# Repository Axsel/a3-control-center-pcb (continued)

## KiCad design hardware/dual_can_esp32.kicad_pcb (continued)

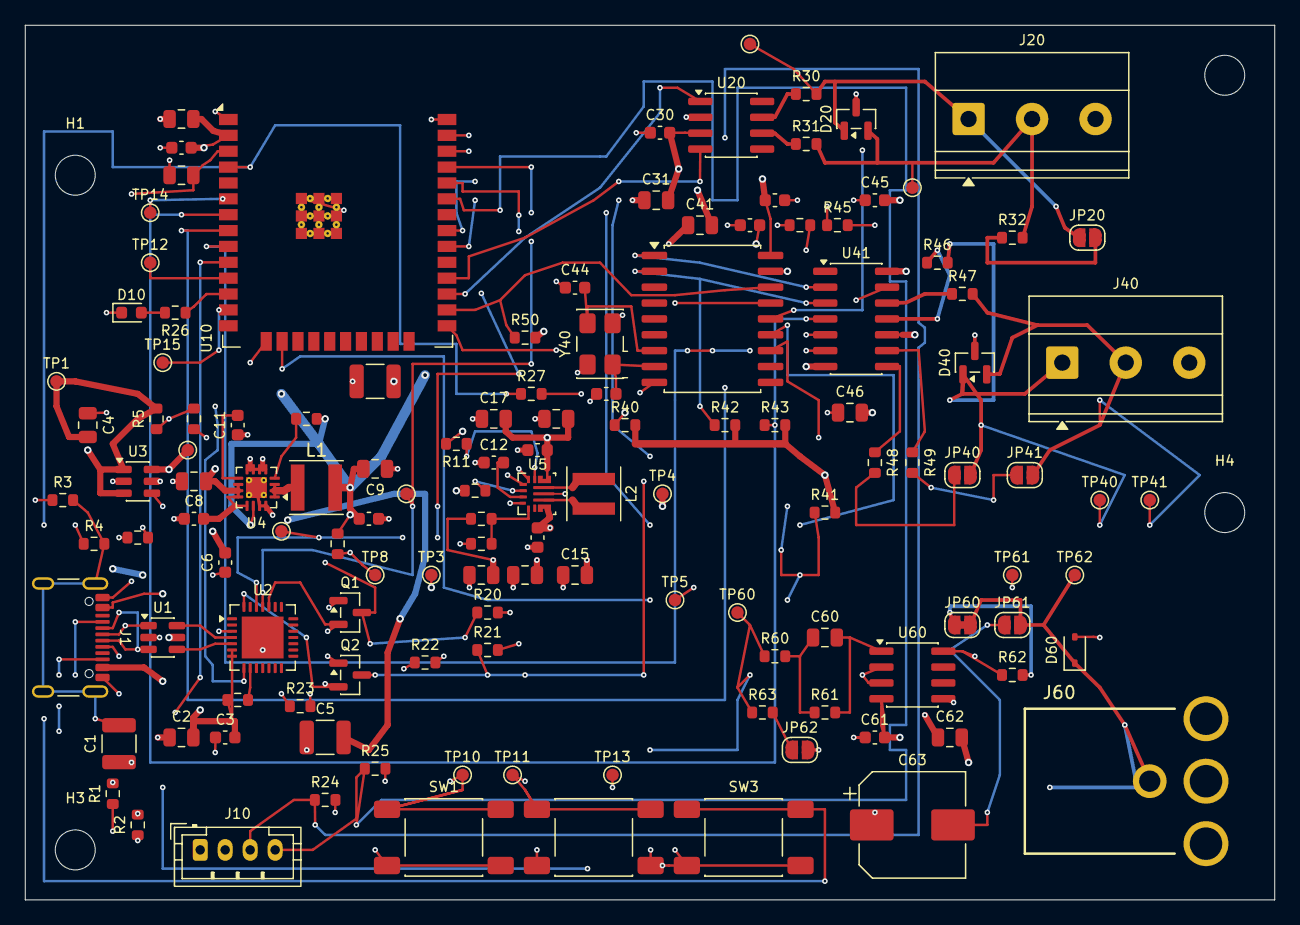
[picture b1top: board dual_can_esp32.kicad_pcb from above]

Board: 4 copper layers, 100.0 x 70.0 mm, 134 parts (0 on the bottom side), 77 nets.

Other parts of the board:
H1, H2, H3, H4: MountingHole_3.2mm_M3

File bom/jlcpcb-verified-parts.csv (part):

Reference,Manufacturer,Manufacturer Part,LCSC Part,Verification date,Catalog state at check,Source,Notes
R1 R2,UNI-ROYAL,0603WAF5101T5E,C23186,2026-10-04,In stock,https://www.lcsc.com/product-detail/C23186.html,"5.1 kohm 1% 100 mW 75 V 0603"
R3,UNI-ROYAL,0603WAF1004T5E,C22935,2026-10-04,In stock,https://www.lcsc.com/product-detail/C22935.html,"1 Mohm 1% 100 mW 75 V 0603"
R5,UNI-ROYAL,0603WAF2212T5E,C25961,2026-10-04,In stock,https://www.lcsc.com/product-detail/C25961.html,"22.1 kohm 1% 100 mW 75 V 0603"
R6,UNI-ROYAL,0603WAF4752T5E,C23061,2026-10-04,In stock,https://www.lcsc.com/product-detail/C23061.html,"47.5 kohm 1% 100 mW 75 V 0603"
R7 R26,UNI-ROYAL,0603WAF1001T5E,C21190,2026-10-04,In stock,https://www.lcsc.com/product-detail/C21190.html,"1 kohm 1% 100 mW 75 V 0603"
R8,UNI-ROYAL,0603WAF2872T5E,C22928,2026-10-04,Low stock (300 shown),https://www.lcsc.com/product-detail/C22928.html,"28.7 kohm 1% 100 mW 75 V 0603; TPS2553 current-limit setpoint"
R9 R11 R20 R21 R22 R23 R27 R40 R41 R42 R43 R44 R45 R50,UNI-ROYAL,0603WAF1002T5E,C25804,2026-10-04,In stock,https://www.lcsc.com/product-detail/C25804.html,"10 kohm 1% 100 mW 75 V 0603"
R10 R14,UNI-ROYAL,0603WAF1003T5E,C25803,2026-10-04,In stock,https://www.lcsc.com/product-detail/C25803.html,"100 kohm 1% 100 mW 75 V 0603"
R12,UNI-ROYAL,0603WAF6803T5E,C25822,2026-10-04,In stock,https://www.lcsc.com/product-detail/C25822.html,"680 kohm 1% 100 mW 75 V 0603; 5V_FT feedback"
R13,UNI-ROYAL,0603WAF1303T5E,C22795,2026-10-04,In stock,https://www.lcsc.com/product-detail/C22795.html,"130 kohm 1% 100 mW 75 V 0603; 5V_FT feedback"
R30 R31 R46 R47,UNI-ROYAL,0603WAF0000T5E,C21189,2026-10-04,In stock,https://www.lcsc.com/product-detail/C21189.html,"0 ohm 100 mW 0603 fitted common-mode-choke bypasses"
R32,UNI-ROYAL,0603WAF1200T5E,C22787,2026-10-04,In stock,https://www.lcsc.com/product-detail/C22787.html,"120 ohm 1% 100 mW 0603 selectable CAN_HS termination"
R48 R49,UNI-ROYAL,0603WAF1201T5E,C22765,2026-10-04,In stock,https://www.lcsc.com/product-detail/C22765.html,"1.2 kohm 1% 100 mW 0603 configurable FT-CAN line terminations"
R60,UNI-ROYAL,0603WAF330JT5E,C23140,2026-10-04,In stock,https://www.lcsc.com/product-detail/C23140.html,"33 ohm 1% 100 mW 0603 DAC isolation"
R62,UNI-ROYAL,0603WAF750JT5E,C4275,2026-10-04,In stock,https://www.lcsc.com/product-detail/C4275.html,"75 ohm 1% 100 mW 0603 video source termination"
D20 D40,Nexperia,PESD2CAN24T-QR,C28933048,2026-10-04,In stock,https://www.lcsc.com/product-detail/C28933048.html,"Reel suffix R; exact PESD2CAN24T-Q device and SOT-23 package"
D60,HXY MOSFET,HPESD5V0U1BA-Q,C25503782,2026-10-05,In stock (900 shown in LCSC catalog; owner reports JLC inventory available),https://www.lcsc.com/product-detail/C25503782.html,"Revision A prototype alternative to Nexperia PESD5V0U1BA-QX/C7508796: same bidirectional 5 V SOD-323 topology; 2.5 pF max; not AEC-Q101; narrower -40 to +125 C operating range and higher 1 uA leakage"
J1,Global Connector Technology,USB4105-GF-A,C3020560,2026-10-04,Out of stock,https://www.lcsc.com/product-detail/USB-Connectors_Global-Co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,"Exact approved connector; mixed SMT contacts/PTH stakes still require assembly-process confirmation"
J10,JST,B4B-PH-K-S(LF)(SN),C131334,2026-10-04,In stock,https://www.lcsc.com/product-detail/C131334.html,"Exact keyed vertical PH-series 4-pin 2.00 mm connector; required JLC manual/wave assembly"
J20 J40,Phoenix Contact,1715734,C480520,2026-10-04,In stock,https://www.lcsc.com/product-detail/C480520.html,"Exact three-independent-position 5.08 mm terminal block; required JLC manual/wave assembly; never substitute internally commoned -B- variant"
J60,Same Sky,RCJ-014,C4991844,2026-10-05,In stock (64 snapshot),https://jlcpcb.com/partdetail/CUI-RCJ014/C4991844,"Yellow right-angle THT RCA; official RCJ-01 footprint; manufacturer pin 1 shell and pin 2 center; JLC manual/wave assembly required"
U1,STMicroelectronics,USBLC6-2SC6,C7519,2026-10-04,Exact product page found,https://www.lcsc.com/product-detail/Diodes-ESD_STMicroelectr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,"Recheck JLC assembly inventory, not only LCSC distributor stock"
U2,Silicon Labs,CP2102N-A02-GQFN28R,C964632,2026-10-04,In stock (40263 shown),https://www.lcsc.com/product-detail/C964632.html,"R is Silicon Labs' optional tape-and-reel suffix; same A02 firmware/hardware revision, temperature grade, QFN28 package, pinout, and land pattern as the former tray-order code"
U3,Texas Instruments,TPS2553DBVR,C55266,2026-10-04,In stock,https://www.lcsc.com/product-detail/C55266.html,"Exact constant-current (non -1 latch-off) variant"
U4,Texas Instruments,TPS62132RGTR,C81563,2026-10-04,Exact product page found,https://www.lcsc.com/product-detail/C81563.html,"Recheck stock and JLC assembly classification at order time"
U5,Texas Instruments,TPS63070RNMR,C109322,2026-10-04,In stock,https://www.lcsc.com/product-detail/C109322.html,"Project-local RNM0015A footprint passed independent dimensional audit; JLC DFM review of the documented pads 4/5 heel relief remains required"
U10,Espressif,ESP32-WROOM-32E-N4,C701341,2026-10-04,In stock,https://www.lcsc.com/product-detail/WIFI-Modules_Espressif-S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,"Exact approved 4 MB PCB-antenna module"
U20,Texas Instruments,TCAN332DR,C73651,2026-10-04,In stock,https://www.lcsc.com/product-detail/C73651.html,"Exact SOIC-8 reel variant"
U40,Microchip,MCP2515T-I/SO,C153782,2026-10-05,In stock (8022 shown; selected in JLC workbook),https://www.lcsc.com/product-detail/C153782.html,"Microchip T prefix denotes tape-and-reel; same 300 mil SOIC-18 industrial-temperature MCP2515 device"
U41,NXP,TJA1055T/3/2Z,C5202584,2026-10-04,Low stock (9 shown),https://www.lcsc.com/product-detail/C5202584.html,"Exact approved /3/2Z variant; likely pre-order/global-source candidate"
U60,Texas Instruments,THS7314DR,C882751,2026-10-04,In stock,https://www.lcsc.com/product-detail/C882751.html,"Exact TI video amplifier; do not use same-named third-party clone"
Y40,Abracon,ABM3BAIG-16.000MHZ-12-2-T,C1986798,2026-10-04,Low stock (5 shown),https://www.lcsc.com/product-detail/C1986798.html,"Exact 16 MHz 12 pF crystal; startup/frequency validation remains required"
C3 C6 C8 C10 C12 C22 C30 C40 C42 C45 C61,Samsung Electro-Mechanics,CL10B104KB8NNNC,C1591,2026-10-04,In stock,https://www.lcsc.com/product-detail/C1591.html,"100 nF 50 V X7R +/-10% 0603 general bypass"
C11,KEMET,C0603C332J5GACTU,C2170675,2026-10-04,In stock (7600 shown),https://www.lcsc.com/product-detail/C2170675.html,"3.3 nF 50 V C0G +/-5% 0603; regulator timing/feed-forward position"
C13 C14 C15,Samsung Electro-Mechanics,CL21A226MOQNNNE,C98190,2026-10-04,In stock,https://www.lcsc.com/product-detail/C98190.html,"22 uF 16 V X5R +/-20% 0805; verify effective capacitance in the TPS63070 power stage"
C16 C19,Samsung Electro-Mechanics,CL10A106MA8NRNC,C96446,2026-10-04,In stock,https://www.lcsc.com/product-detail/C96446.html,"10 uF 25 V X5R +/-20% 0603"
C7 C17 C18 C21,Samsung Electro-Mechanics,CL21A106KAYNNNE,C15850,2026-10-04,In stock,https://www.lcsc.com/product-detail/C15850.html,"10 uF 25 V X5R +/-10% 0805; generous voltage margin"
C2,Samsung Electro-Mechanics,CL21B475KOFNNNE,C107365,2026-10-04,In stock,https://www.lcsc.com/product-detail/C107365.html,"4.7 uF 16 V X7R +/-10% 0805"
C4 C20 C31 C41 C46 C62,Samsung Electro-Mechanics,CL21B105KAFNNNE,C116352,2026-10-04,In stock,https://www.lcsc.com/product-detail/C116352.html,"1 uF 25 V X7R +/-10% 0805"
C9,Samsung Electro-Mechanics,CL21A226MPQNNNE,C29277,2026-10-04,In stock,https://www.lcsc.com/product-detail/C29277.html,"22 uF 10 V X5R +/-20% 0805 on 3.3 V rail"
C43 C44,Samsung Electro-Mechanics,CL10C180JB8NNNC,C1647,2026-10-04,In stock,https://www.lcsc.com/product-detail/C1647.html,"18 pF 50 V C0G +/-5% 0603 crystal load capacitors"
C5,Samsung Electro-Mechanics,CL32A476KPJNNNE,C525654,2026-10-04,In stock (635 shown),https://www.lcsc.com/product-detail/C525654.html,"47 uF 10 V X5R +/-10% 1210 on USB 5 V; effective-capacitance review retained"
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
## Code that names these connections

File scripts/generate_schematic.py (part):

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        MPN="USB4105-GF-A",
    )
    for pin in ("A4", "A9", "B4", "B9"):
        net(s, "VBUS_RAW", "J1", pin)
    for pin in ("A1", "A12", "B1", "B12"):
        net(s, "GND", "J1", pin)
    for pin in ("A6", "B6"):
        net(s, "USB_CONN_DP", "J1", pin)
    for pin in ("A7", "B7"):
        net(s, "USB_CONN_DM", "J1", pin)
    net(s, "USB_CC1", "J1", "A5")
    net(s, "USB_CC2", "J1", "B5")
    net(s, "USB_SHIELD", "J1", "SH")
    nc(s, "J1", "A8", "B8")

    two_pin(s, "Device:R", "R1", "5.1k 1%", (25, 82), "USB_CC1", "GND", R0603)
    two_pin(s, "Device:R", "R2", "5.1k 1%", (35, 82), "USB_CC2", "GND", R0603)
    two_pin(s, "Device:R", "R3", "1M", (45, 82), "USB_SHIELD", "GND", R0603)
    two_pin(s, "Device:C", "C1", "4.7nF 1kV C0G | FV32N472J102EFG", (55, 82), "USB_SHIELD", "GND", C1210)
    two_pin(s, "Device:R", "R4", "0R DNP", (65, 82), "USB_SHIELD", "GND", R0603)

    component(s, "Power_Protection:USBLC6-2SC6", "U1", "USBLC6-2SC6", (72, 55), "Package_TO_SOT_SMD:SOT-23-6")
    net(s, "USB_CONN_DP", "U1", "1")
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    net(s, "USB_DTR", "U2", "28")
    nc(s, "U2", "1", "2", "10", "11", "12", "13", "14", "15", "16", "17", "18", "19", "20", "21", "22", "23", "27")

    two_pin(s, "Device:R", "R5", "22.1k 1%", (90, 82), "VBUS_RAW", "USB_VBUS_SENSE", R0603)
    two_pin(s, "Device:R", "R6", "47.5k 1%", (100, 82), "USB_VBUS_SENSE", "GND", R0603)
    two_pin(s, "Device:R", "R7", "1k", (110, 82), "+3V3", "CP2102_RST", R0603)
    two_pin(s, "Device:C", "C2", "4.7uF", (120, 82), "+3V3", "GND", C0805)
    two_pin(s, "Device:C", "C3", "100nF", (130, 82), "+3V3", "GND", C0603)

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    net(s, "USB_PWR_FAULT", "U3", "4")
    net(s, "USB_ILIM", "U3", "5")
    net(s, "+5V_USB", "U3", "6")
    two_pin(s, "Device:R", "R8", "28.7k 1%", (30, 132), "USB_ILIM", "GND", R0603)
    two_pin(s, "Device:R", "R9", "10k", (40, 132), "+3V3", "USB_PWR_FAULT", R0603)
    two_pin(s, "Device:C", "C4", "1uF", (50, 132), "VBUS_RAW", "GND", C0805)
    two_pin(s, "Device:C", "C5", "47uF", (60, 132), "+5V_USB", "GND", C1210)
    two_pin(s, "Device:C", "C6", "100nF", (70, 132), "+5V_USB", "GND", C0603)

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        "Package_DFN_QFN:VQFN-16-1EP_3x3mm_P0.5mm_EP1.68x1.68mm_ThermalVias",
    )
    for pin in ("1", "2", "3"):
        net(s, "SW_3V3", "U4", pin)
    net(s, "PG_3V3", "U4", "4")
    net(s, "GND", "U4", "5")
    net(s, "GND", "U4", "6")
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    net(s, "+3V3", "U4", "14")
    for pin in ("15", "16", "17"):
        net(s, "GND", "U4", pin)
    two_pin(s, "Device:L", "L1", "2.2uH WPN4020H2R2MT", (130, 107), "SW_3V3", "+3V3", "A3_Control_Center:WPN4020H", rotation=0, Datasheet="https://www.alfatec.de/fileadmin/productfiles/datasheets/sunlord_wpn4020h_series.pdf")
    two_pin(s, "Device:C", "C7", "10uF", (85, 132), "+5V_USB", "GND", C0805)
    two_pin(s, "Device:C", "C8", "100nF", (95, 132), "+5V_USB", "GND", C0603)
    two_pin(s, "Device:C", "C9", "22uF", (105, 132), "+3V3", "GND", C0805)
    two_pin(s, "Device:C", "C10", "100nF", (115, 132), "+3V3", "GND", C0603)
    two_pin(s, "Device:C", "C11", "3.3nF", (125, 132), "SS_3V3", "GND", C0603)
    two_pin(s, "Device:R", "R10", "100k", (135, 132), "+3V3", "PG_3V3", R0603)

    component(s, "a3-control-center:TPS63070", "U5", "TPS63070RNMR", (172, 110), "A3_Control_Center:TI_RNM0015A_VQFN-HR-15")
    net(s, "GND", "U5", "1")
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        net(s, "+5V_USB", "U5", pin)
    net(s, "EN_5VFT", "U5", "14")
    net(s, "GND", "U5", "15")
    two_pin(s, "Device:L", "L2", "1.5uH XGL4020-152MEC", (172, 142), "L1_5VFT", "L2_5VFT", "Inductor_SMD:L_Coilcraft_XxL4020", rotation=0)
    two_pin(s, "Device:R", "R11", "10k", (145, 132), "+5V_USB", "EN_5VFT", R0603)
    two_pin(s, "Device:R", "R12", "680k 1%", (155, 132), "+5V_FT", "FB_5VFT", R0603)
    two_pin(s, "Device:R", "R13", "130k 1%", (165, 132), "FB_5VFT", "GND", R0603)
    two_pin(s, "Device:R", "R14", "100k", (175, 132), "+3V3", "PG_5VFT", R0603)
    two_pin(s, "Device:C", "C12", "100nF", (185, 132), "VAUX_5VFT", "GND", C0603)
    for i, x in enumerate((195, 205, 215), 13):
        two_pin(s, "Device:C", f"C{i}", "22uF 16V", (x, 132), "+5V_FT", "GND", C0805)
    two_pin(s, "Device:C", "C16", "10uF", (225, 132), "+5V_FT", "GND", C0603)
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    net(s, "ESP_EN", "U10", "3")
    net(s, "USER_BUTTON", "U10", "4")
    nc(s, "U10", "5")
    net(s, "EXP_GPIO34", "U10", "6")
    net(s, "CAN_FT_ERR", "U10", "7")
    net(s, "CAN_FT_STB", "U10", "8")
    net(s, "CAN_FT_EN", "U10", "9")
    net(s, "VIDEO_DAC", "U10", "10")
    net(s, "DAC2_RESERVED", "U10", "11")
    net(s, "STATUS_LED", "U10", "12")
    net(s, "EXP_GPIO14", "U10", "13")
    nc(s, "U10", "14")
    net(s, "CAN_FT_INT", "U10", "16")
    nc(s, "U10", "17", "18", "19", "20", "21", "22", "23", "24")
    net(s, "ESP_GPIO0", "U10", "25")
    net(s, "CAN_FT_CS", "U10", "26")
    net(s, "CAN_HS_TX", "U10", "27")
    net(s, "CAN_HS_RX", "U10", "28")
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    net(s, "CAN_FT_MOSI", "U10", "37")
    net(s, "GND", "U10", "[1,15,38,39]")

    two_pin(s, "Device:R", "R20", "10k", (35, 45), "+3V3", "ESP_EN", R0603)
    two_pin(s, "Device:C", "C20", "1uF", (45, 45), "ESP_EN", "GND", C0805)
    component(s, "Switch:SW_Push", "SW1", "RESET / EN", (55, 45), BUTTON)
    net(s, "ESP_EN", "SW1", "1")
    net(s, "GND", "SW1", "2")
    two_pin(s, "Device:R", "R21", "10k", (35, 62), "+3V3", "ESP_GPIO0", R0603)
    component(s, "Switch:SW_Push", "SW2", "BOOT", (55, 62), BUTTON)
    net(s, "ESP_GPIO0", "SW2", "1")
    net(s, "GND", "SW2", "2")

    # The generator does not retain KiCad's inherited-symbol hash for SS8050.
    # Use the equivalent B-E-C base graphic and keep the audited value/package.
    component(s, "Transistor_BJT:Q_NPN_BEC", "Q1", "SS8050", (35, 92), "Package_TO_SOT_SMD:SOT-23", Manufacturer="onsemi", MPN="SS8050")
    component(s, "Transistor_BJT:Q_NPN_BEC", "Q2", "SS8050", (60, 92), "Package_TO_SOT_SMD:SOT-23", Manufacturer="onsemi", MPN="SS8050")
    two_pin(s, "Device:R", "R22", "10k", (25, 108), "USB_DTR", "AUTO_Q1_BASE", R0603, rotation=0)
    two_pin(s, "Device:R", "R23", "10k", (50, 108), "USB_RTS", "AUTO_Q2_BASE", R0603, rotation=0)
    net(s, "AUTO_Q1_BASE", "Q1", "1")
    net(s, "USB_RTS", "Q1", "2")
    net(s, "ESP_EN", "Q1", "3")
    net(s, "AUTO_Q2_BASE", "Q2", "1")
    net(s, "USB_DTR", "Q2", "2")
    net(s, "ESP_GPIO0", "Q2", "3")
    s.add_text("Espressif crossed two-NPN auto-program circuit: simultaneous DTR/RTS assertion leaves EN and GPIO0 high.", (25, 118), size=1.0)

    two_pin(s, "Device:C", "C21", "10uF", (132, 43), "+3V3", "GND", C0805)
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    net(s, "GND", "J10", "2")
    net(s, "OLED_SCL", "J10", "3")
    net(s, "OLED_SDA", "J10", "4")
    two_pin(s, "Device:R", "R24", "4.7k DNP", (175, 85), "+3V3", "OLED_SCL", R0603)
    two_pin(s, "Device:R", "R25", "4.7k DNP", (185, 85), "+3V3", "OLED_SDA", R0603)
    s.add_text("J10 Gravity/PH2.0: 1 +3V3, 2 GND, 3 SCL, 4 SDA. DFR0486 has onboard 10k pull-ups; R24/R25 stay DNP.", (150, 95), size=1.0)

    two_pin(s, "Device:R", "R26", "1k", (175, 112), "STATUS_LED", "STATUS_LED_A", R0603, rotation=0)
    component(s, "Device:LED", "D10", "STATUS GREEN", (200, 112), "LED_SMD:LED_0603_1608Metric", rotation=90)
    net(s, "STATUS_LED_A", "D10", "1")
    net(s, "GND", "D10", "2")
    two_pin(s, "Device:R", "R27", "10k", (175, 128), "+3V3", "USER_BUTTON", R0603)
    component(s, "Switch:SW_Push", "SW3", "USER", (200, 128), BUTTON)
    net(s, "USER_BUTTON", "SW3", "1")
    net(s, "GND", "SW3", "2")

    testpoint(s, "TP10", "ESP_EN", (25, 140))
    testpoint(s, "TP11", "ESP_GPIO0", (40, 140))
    testpoint(s, "TP12", "DAC2_RESERVED", (55, 140))
    testpoint(s, "TP13", "VIDEO_DAC", (70, 140))
    testpoint(s, "TP14", "EXP_GPIO34", (85, 140))
    testpoint(s, "TP15", "EXP_GPIO14", (100, 140))

    s.save(HW / "dual_can_esp32_mcu_ui.kicad_sch")

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
    # Default-fit bypasses. Their four pads reserve the series position where
    # a validated two-line common-mode choke may replace both links later.
    two_pin(s, "Device:R", "R30", "0R (CMC bypass)", (125, 58), "CAN_HS_H_PHY", "CAN_HS_H", R0603, rotation=0)
    two_pin(s, "Device:R", "R31", "0R (CMC bypass)", (125, 72), "CAN_HS_L_PHY", "CAN_HS_L", R0603, rotation=0)

    component(s, "a3-control-center:PESD2CAN24T_Q", "D20", "PESD2CAN24T-Q", (160, 65), "Package_TO_SOT_SMD:SOT-23")
    net(s, "CAN_HS_H", "D20", "1")
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    component(s, "Jumper:SolderJumper_2_Open", "JP20", "CAN_HS TERM ENABLE", (155, 100), "Jumper:SolderJumper-2_P1.3mm_Open_RoundedPad1.0x1.5mm")
    net(s, "CAN_HS_H", "JP20", "1")
    net(s, "CAN_HS_TERM", "JP20", "2")
    two_pin(s, "Device:R", "R32", "120R 1%", (180, 100), "CAN_HS_TERM", "CAN_HS_L", R0603, rotation=0)
    s.add_text("JP20: bridge only when this board is at a physical bus end.", (160, 112), size=1.0)

    component(s, "Connector_Generic:Conn_01x03", "J20", "1715734", (205, 65), "TerminalBlock_Phoenix:TerminalBlock_Phoenix_MKDS-1,5-3-5.08_1x03_P5.08mm_Horizontal")
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    net(s, "+3V3", "U40", "18")
    two_pin(s, "Device:C", "C40", "100nF", (35, 105), "+3V3", "GND", C0603)
    two_pin(s, "Device:C", "C41", "1uF", (45, 105), "+3V3", "GND", C0805)
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
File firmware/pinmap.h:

#pragma once

/* ESP32-WROOM-32E-N4 hardware contract; keep synchronized with docs/pinout.md. */

#define PIN_UART0_TX          1
#define PIN_UART0_RX          3
#define PIN_BOOT              0

#define PIN_CAN_HS_TX        16
#define PIN_CAN_HS_RX        17

#define PIN_CAN_FT_SCK       18
#define PIN_CAN_FT_MISO      19
#define PIN_CAN_FT_MOSI      23
#define PIN_CAN_FT_CS         4
#define PIN_CAN_FT_INT       13
#define PIN_CAN_FT_STB       32
#define PIN_CAN_FT_EN        33
#define PIN_CAN_FT_ERR       35

#define PIN_OLED_SDA         21
#define PIN_OLED_SCL         22

#define PIN_VIDEO_DAC        25
#define PIN_DAC2_RESERVED    26

#define PIN_STATUS_LED       27
#define PIN_USER_BUTTON      36
#define PIN_EXP_GPIO34       34
#define PIN_EXP_GPIO14       14

#define MCP2515_OSC_HZ 16000000UL
#define CAN_FT_MAX_BITRATE 125000UL
